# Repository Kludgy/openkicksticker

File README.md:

Open Kicksticker for Amiga 500+
===============================

This repository holds KiCad files for a latching quad Kickstart switcher designed to socket into an Amiga 500+. As with other quad switchers out in the wild, this also selects between 4 different 512KB banks from M27C160 using JP0 & JP1 to pull high address lines A18 & A19 high, respectively. The unique feature of this switch is that it will not actually switch to a new bank until after the keyboard reset signal (connect to ~ROM_KBRESET) is finished asserting low. This prevents the active ROM data from changing while it is in use.

BOM:
* ROM_U1: 1x 42-pin DIL socket (and programmed M27C160 EPROM).
* ROM_A1: 2x 1x20 turned pin headers for the bottom of the board. (Go for lower-profile pins to make this fit under the KB in an A500 model, otherwise it is a couple mm too high.)
* ROM_U2: 1x 74AHC273 or equivalent octal latching D-type flipflop IC.
* R1: 1k axial resistor.
* R2-3: 2x 4k7 axial resistor. These should be small enough to fit under the M27C160 after it is installed. 1/4W metal film is fine.
* C1: 1x 10pF small bipolar cap for power-up reset delay.
* C2: 1x 0.1uF small bipolar cap for bypass.

There is probably a lot of fudge room to substitute similar parts in practice, such as larger-F capacitors for C1 and C2, or perhaps a lower speed ROM_U2 flipflop IC depending on what you may have on hand.

Notes
-----

* The current layout tends to be slightly too high to fit under the keyboard in an A500 case. Layout could be altered to push the ROM socket back away from the keyboard a couple more cm to solve this.
* The layout could use revision for smaller footprints. (An SMD variant would easily fit all parts completely under the ROM_U1 socket.)
* This should work in other (later) Amiga 500 motherboard revisions, or in the Amiga 2000, but no work has been done to verify this.
* A minor revision may make this compatible with earlier Amiga 500 motherboard revisions.

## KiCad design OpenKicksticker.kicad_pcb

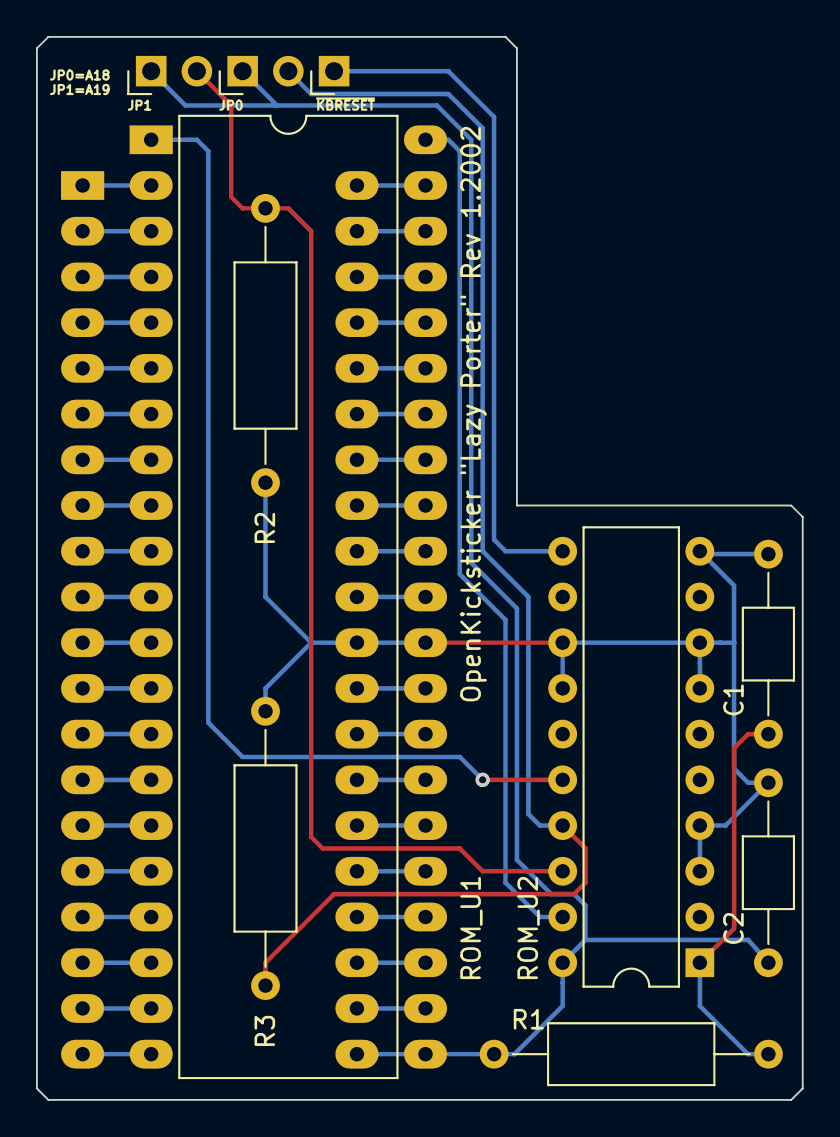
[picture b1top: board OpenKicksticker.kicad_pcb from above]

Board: 2 copper layers, 42.5 x 59.1 mm, 10 parts (0 on the bottom side), 45 nets.

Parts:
C1: 10pF; C_Axial_L3.8mm_D2.6mm_P10.00mm_Horizontal
C2: 0.1uF; C_Axial_L3.8mm_D2.6mm_P10.00mm_Horizontal
JP0: JP0; PinHeader_1x02_P2.54mm_Horizontal
JP1: JP1; PinHeader_1x02_P2.54mm_Horizontal
R1: 1k; R_Axial_DIN0309_L9.0mm_D3.2mm_P15.24mm_Horizontal
R2, R3: 4k7; R_Axial_DIN0309_L9.0mm_D3.2mm_P15.24mm_Horizontal
ROM_A1: 27C400_Amiga_Driver; DIP-40_W15.24mm_LongPads
ROM_U1: M27C160 SOCKET; DIP-42_W15.24mm_Socket_LongPads
ROM_U2: 74AHC273; DIP-20_W7.62mm

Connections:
/a0: ROM_A1.9, ROM_U1.10
/a1: ROM_A1.8, ROM_U1.9
/a2: ROM_A1.7, ROM_U1.8
/a3: ROM_A1.6, ROM_U1.7
/a4: ROM_A1.5, ROM_U1.6
/a5: ROM_A1.4, ROM_U1.5
/a6: ROM_A1.3, ROM_U1.4
/a7: ROM_A1.2, ROM_U1.3
/a8: ROM_A1.40, ROM_U1.41
/a9: ROM_A1.39, ROM_U1.40
/a10: ROM_A1.38, ROM_U1.39
/a11: ROM_A1.37, ROM_U1.38
/a12: ROM_A1.36, ROM_U1.37
/a13: ROM_A1.35, ROM_U1.36
/a14: ROM_A1.34, ROM_U1.35
/a15: ROM_A1.33, ROM_U1.34
/a16: ROM_A1.32, ROM_U1.33
/a17: ROM_A1.1, ROM_U1.2
/d0: ROM_A1.13, ROM_U1.14
/d1: ROM_A1.15, ROM_U1.16
/d2: ROM_A1.17, ROM_U1.18
/d3: ROM_A1.19, ROM_U1.20
/d4: ROM_A1.22, ROM_U1.23
/d5: ROM_A1.24, ROM_U1.25
/d6: ROM_A1.26, ROM_U1.27
/d7: ROM_A1.28, ROM_U1.29
/d8: ROM_A1.14, ROM_U1.15
/d9: ROM_A1.16, ROM_U1.17
/d10: ROM_A1.18, ROM_U1.19
/d11: ROM_A1.20, ROM_U1.21
/d12: ROM_A1.23, ROM_U1.24
/d13: ROM_A1.25, ROM_U1.26
/d14: ROM_A1.27, ROM_U1.28
/d15: ROM_A1.29, ROM_U1.30
/vpp: ROM_A1.31, ROM_U1.32
/~ce: ROM_A1.10, ROM_U1.11
/~oe: ROM_A1.12, ROM_U1.13
unnamed: C1.1, R1.2, ROM_U2.1
unnamed: C1.2, C2.2, R2.2, R3.2, ROM_A1.30, ROM_U1.31, ROM_U2.3, ROM_U2.4, ROM_U2.7, ROM_U2.8, ROM_U2.10, ROM_U2.13, ROM_U2.14
unnamed: C2.1, JP0.1, JP1.1, R1.1, ROM_A1.21, ROM_U1.22, ROM_U2.20
unnamed: JP1.2, R2.1, ROM_U2.18
unnamed: JP0.2, R3.1, ROM_U2.17
unnamed: ROM_A1.11, ROM_U1.12
unnamed: ROM_U1.1, ROM_U2.16
unnamed: ROM_U1.42, ROM_U2.19

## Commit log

2020-02-22 replace readme with correct content
2020-02-22 remove grammatically misleading Rev 1.2002
2020-02-22 typo
2020-02-23 license
2020-04-19 tweak readme to include info about fit in A500 cases
